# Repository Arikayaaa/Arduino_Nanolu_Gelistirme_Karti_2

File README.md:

# Arduino_Nanolu_Gelistirme_Karti_2

* Arduino Nano
* L393D Motor Driver
* Cizgi İzleyen Sensör Konnekörü
* HC-SR04 Mesafe Sensörü Konnektörü
* Bluetooth Konnektörü
* LM35 Sıcaklık Sensörü
* Infrared Sensör
* WS18B20 LED
* Servo Motor Konnektörü
* LDR
* Buzzer
* I2C Bağlantı Konnektörü

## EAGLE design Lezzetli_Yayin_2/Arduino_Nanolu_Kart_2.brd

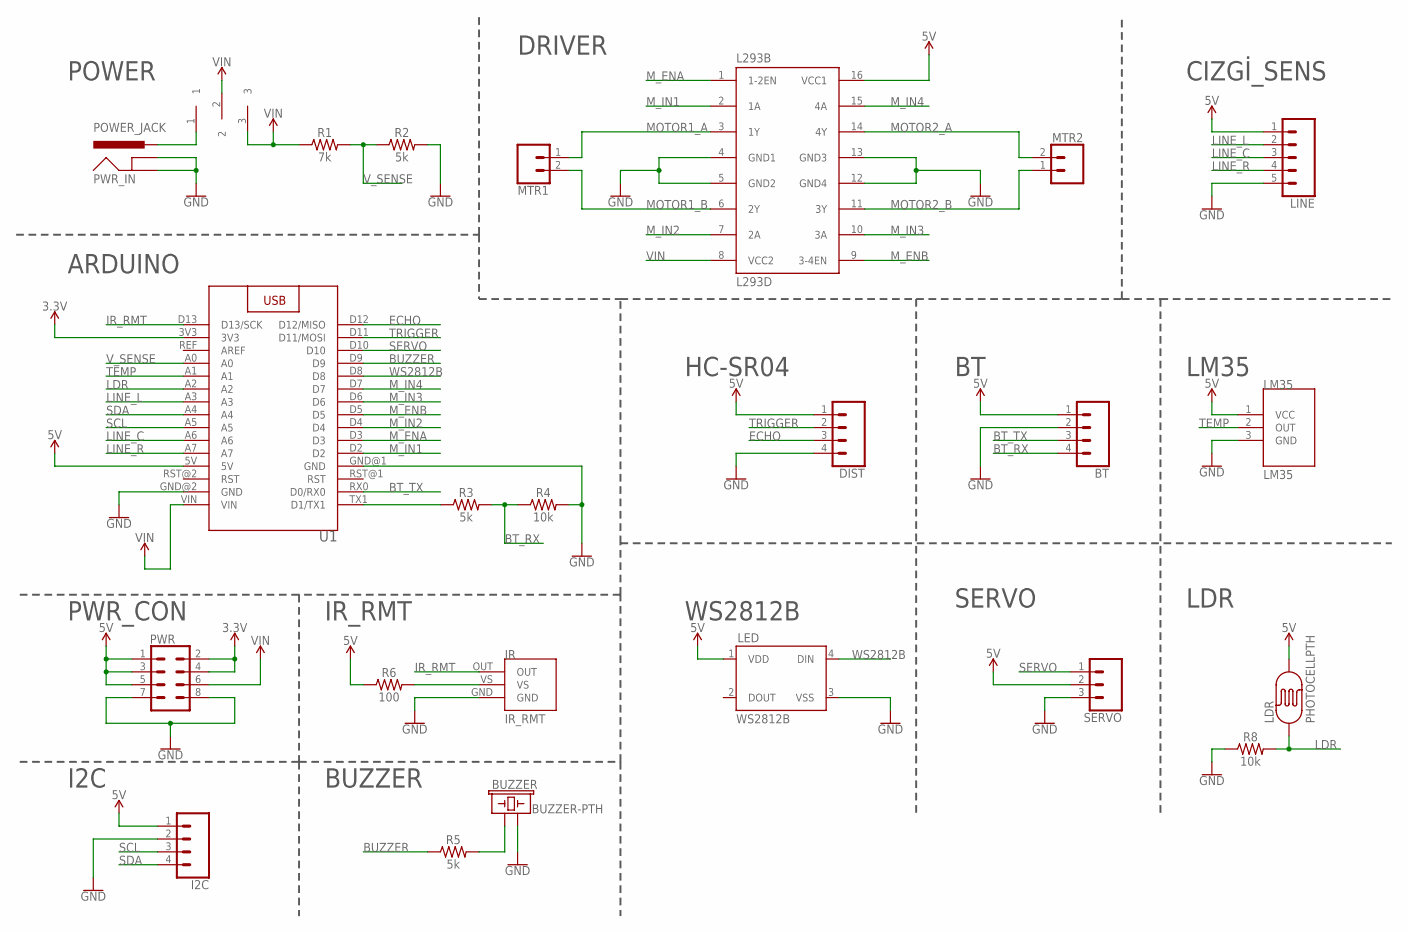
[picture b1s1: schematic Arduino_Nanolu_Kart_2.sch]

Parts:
BT: CONN_04; 1X04
BUZZER: BUZZER-PTH; BUZZER-12MM
DIST: CONN_04; 1X04
I2C: CONN_04; 1X04
IR: IR_RMT; IR_SENSOR
L293B: L293D; DIL16
LDR: PHOTOCELLPTH; PHOTOCELL
LED: WS2812B
LINE: CONN_05; 1X05
LM35: LM35; TO-92
MTR1, MTR2: CONN_023.5MM; SCREWTERMINAL-3.5MM-2
PWR: CONN_04X2; 2X4
PWR_IN: POWER_JACK; POWER_JACK_PTH
R1: 7k; AXIAL-0.3
R2, R3, R5: 5k; AXIAL-0.3
R4, R8: 10k; AXIAL-0.3
R6: 100; AXIAL-0.3
SERVO: CONN_03; 1X03
SWICH: SWICH_X2_3MM
U1: ARDUINO_NANO

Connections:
3.3V: PWR.2, PWR.4, U1.3V3
5V: BT.1, DIST.1, I2C.1, L293B.16 (VCC1), LDR.2, LED.1 (VDD), LINE.1, LM35.1 (VCC), PWR.1, PWR.3, PWR.5, R6.P$1 (1), SERVO.2, U1.5V
BT_RX: BT.4, R3.P$2 (2), R4.P$1 (1)
BT_TX: BT.3, U1.RX0 (D0/RX0)
BUZZER: R5.P$1 (1), U1.D9
ECHO: DIST.3, U1.D12 (D12/MISO)
GND: BT.2, BUZZER.- (2), DIST.4, I2C.2, IR.GND, L293B.4 (GND1), L293B.5 (GND2), L293B.12 (GND4), L293B.13 (GND3), LED.3 (VSS), LINE.5, LM35.3 (GND), PWR.7, PWR.8, PWR_IN.GND, PWR_IN.GNDBREAK, R2.P$2 (2), R4.P$2 (2), R8.P$1 (1), SERVO.3, U1.GND@1 (GND), U1.GND@2 (GND)
IR_RMT: IR.OUT, U1.D13 (D13/SCK)
LDR: LDR.1, R8.P$2 (2), U1.A2
LINE_C: LINE.3, U1.A6
LINE_L: LINE.2, U1.A3
LINE_R: LINE.4, U1.A7
MOTOR1_A: L293B.3 (1Y), MTR1.1
MOTOR1_B: L293B.6 (2Y), MTR1.2
MOTOR2_A: L293B.14 (4Y), MTR2.2
MOTOR2_B: L293B.11 (3Y), MTR2.1
M_ENA: L293B.1 (1-2EN), U1.D3
M_ENB: L293B.9 (3-4EN), U1.D5
M_IN1: L293B.2 (1A), U1.D2
M_IN2: L293B.7 (2A), U1.D4
M_IN3: L293B.10 (3A), U1.D6
M_IN4: L293B.15 (4A), U1.D7
unnamed: R3.P$1 (1), U1.TX1 (D1/TX1)
unnamed: BUZZER.+ (1), R5.P$2 (2)
unnamed: IR.VS, R6.P$2 (2)
unnamed: PWR_IN.PWR, SWICH.1
SCL: I2C.3, U1.A5
SDA: I2C.4, U1.A4
SERVO: SERVO.1, U1.D10
TEMP: LM35.2 (OUT), U1.A1
TRIGGER: DIST.2, U1.D11 (D11/MOSI)
VIN: L293B.8 (VCC2), PWR.6, R1.P$1 (1), SWICH.2, SWICH.3, U1.VIN
V_SENSE: R1.P$2 (2), R2.P$1 (1), U1.A0
WS2812B: LED.4 (DIN), U1.D8

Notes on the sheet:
POWER
ARDUINO
DRIVER
PWR_CON
I2C
IR_RMT
BUZZER
HC-SR04
WS2812B
LM35
CIZGİ_SENS
LDR
SERVO

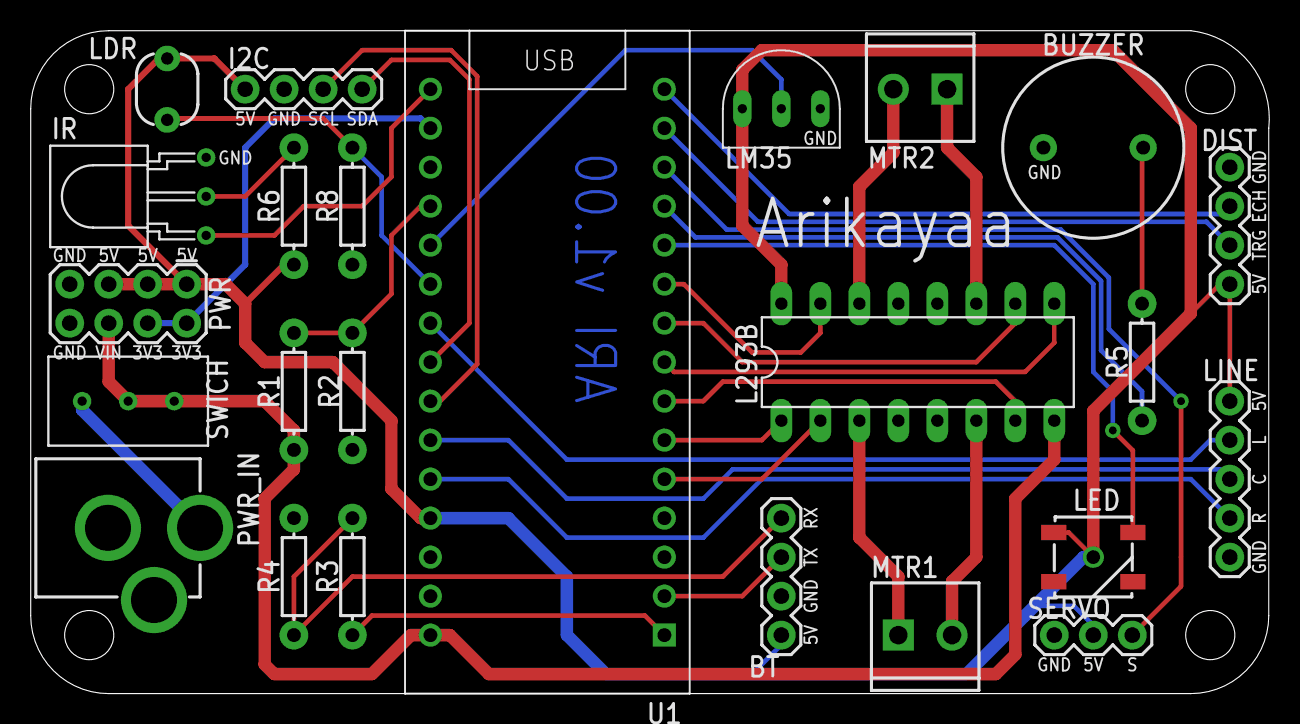
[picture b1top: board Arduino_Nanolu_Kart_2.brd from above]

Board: 2 copper layers, 80.7 x 43.2 mm, 24 parts (0 on the bottom side), 34 nets.

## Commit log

2020-05-25 v1.00
    Cesitli sensorlere uyumludur
2022-05-19 v1.00
    Gereksiz kurtarma dosyaları silindi.

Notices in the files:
parts and their libraries:
SparkFun-Connectors: Licensing: Creative Commons ShareAlike 4.0 International - https://creativecommons.org/licenses/by-sa/4.0
SparkFun-LED: Licensing: CC v3.0 Share-Alike You are welcome to use this library for commercial purposes.
